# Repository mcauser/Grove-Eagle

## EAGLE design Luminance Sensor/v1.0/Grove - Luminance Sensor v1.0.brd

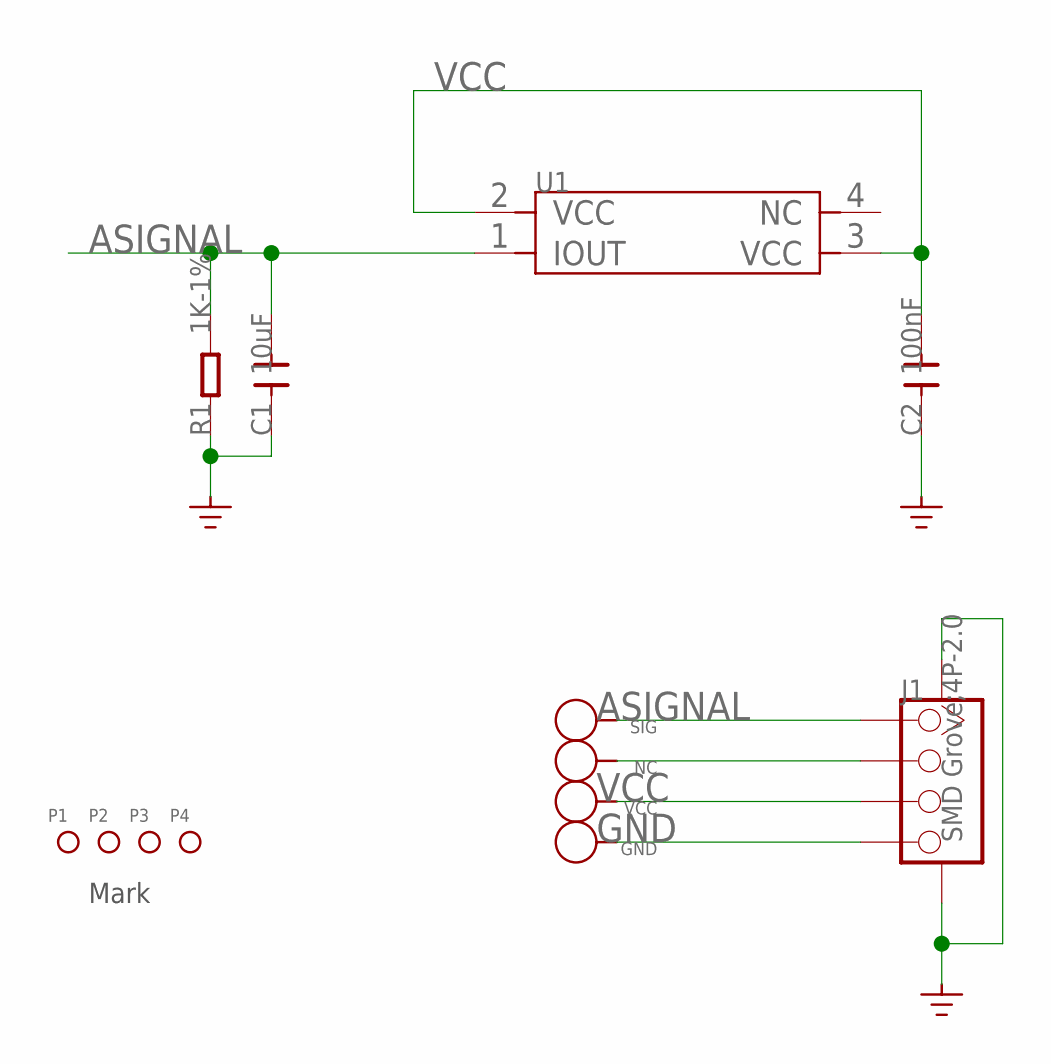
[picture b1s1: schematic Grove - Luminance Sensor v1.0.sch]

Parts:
C1: 10uF; C0603
C2: 100nF; C0603
GND: PAD-TEST-POINT'4545'; TP_4545
J1: SMD Grove;4P-2.0; 4P-SMD-2.0
NC: PAD-TEST-POINT'4545'; TP_4545
P1, P2, P3, P4: PAD-MARK; ROUND-MARK-1.0
R1: 1K-1%; R0603
SIG: PAD-TEST-POINT'4545'; TP_4545
U1: SENSOR-APDS-9002; 4P-SMD-2X1.25X0.8H
VCC: PAD-TEST-POINT'4545'; TP_4545

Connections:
ASIGNAL: C1.2, J1.1, R1.2, SIG.T, U1.1 (IOUT)
GND: C1.1, C2.1, GND.T, J1.4, J1.SS1, J1.SS2, R1.1
unnamed: J1.2, NC.T
VCC: C2.2, J1.3, U1.2 (VCC), U1.3 (VCC), VCC.T

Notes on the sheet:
Mark

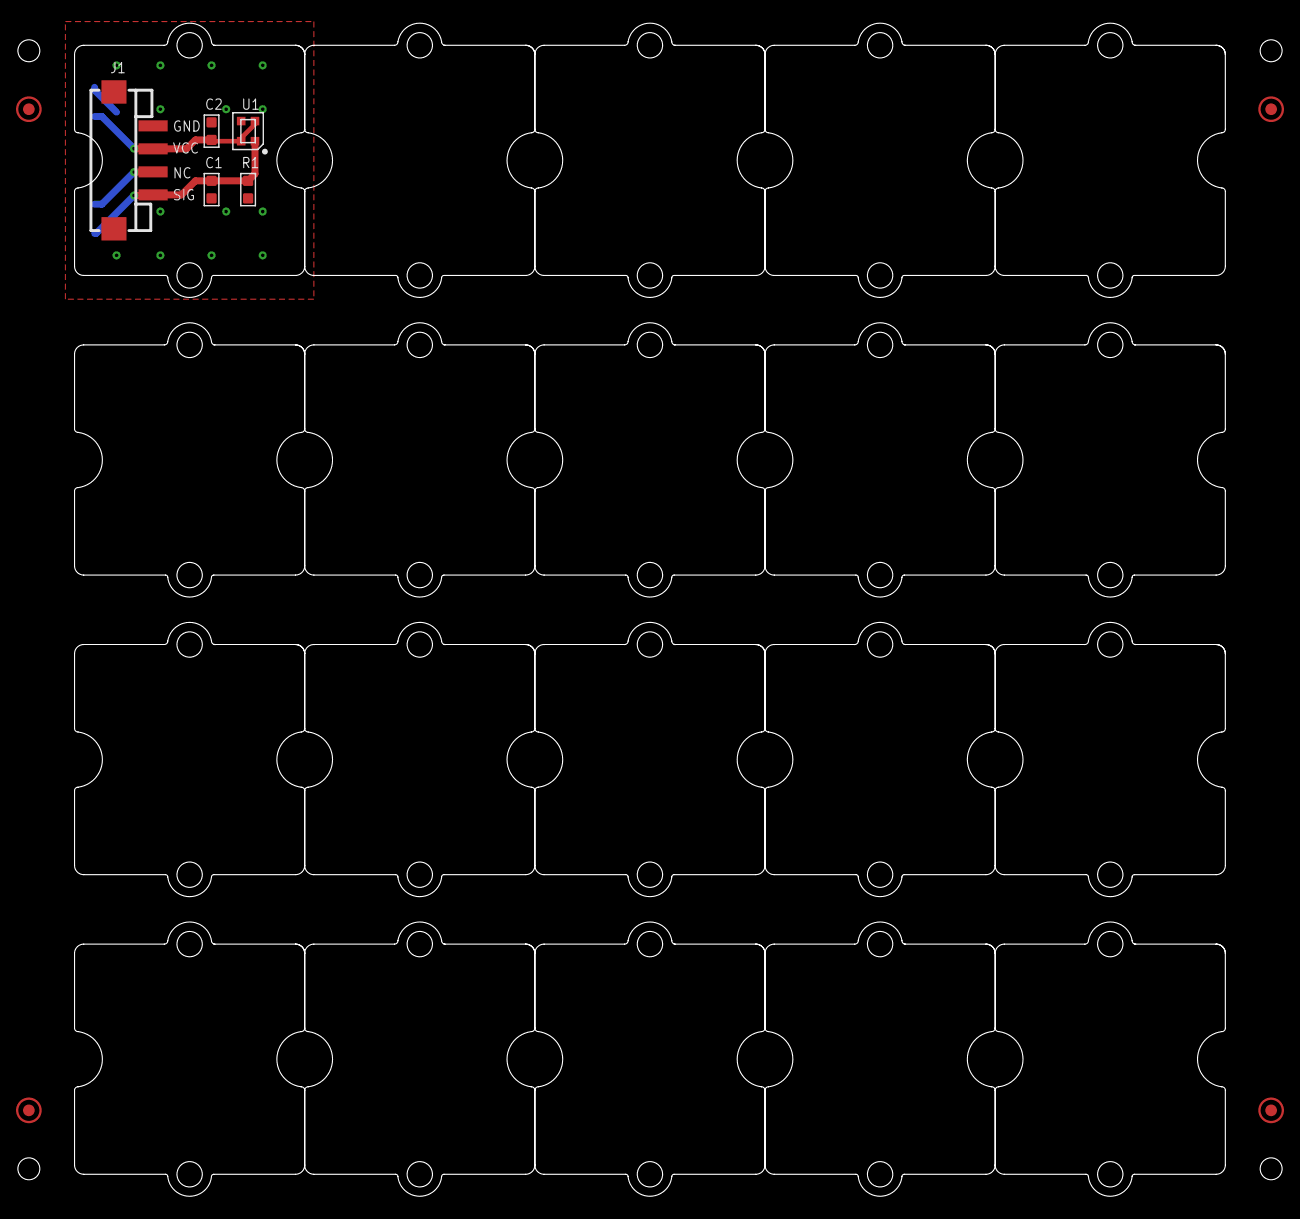
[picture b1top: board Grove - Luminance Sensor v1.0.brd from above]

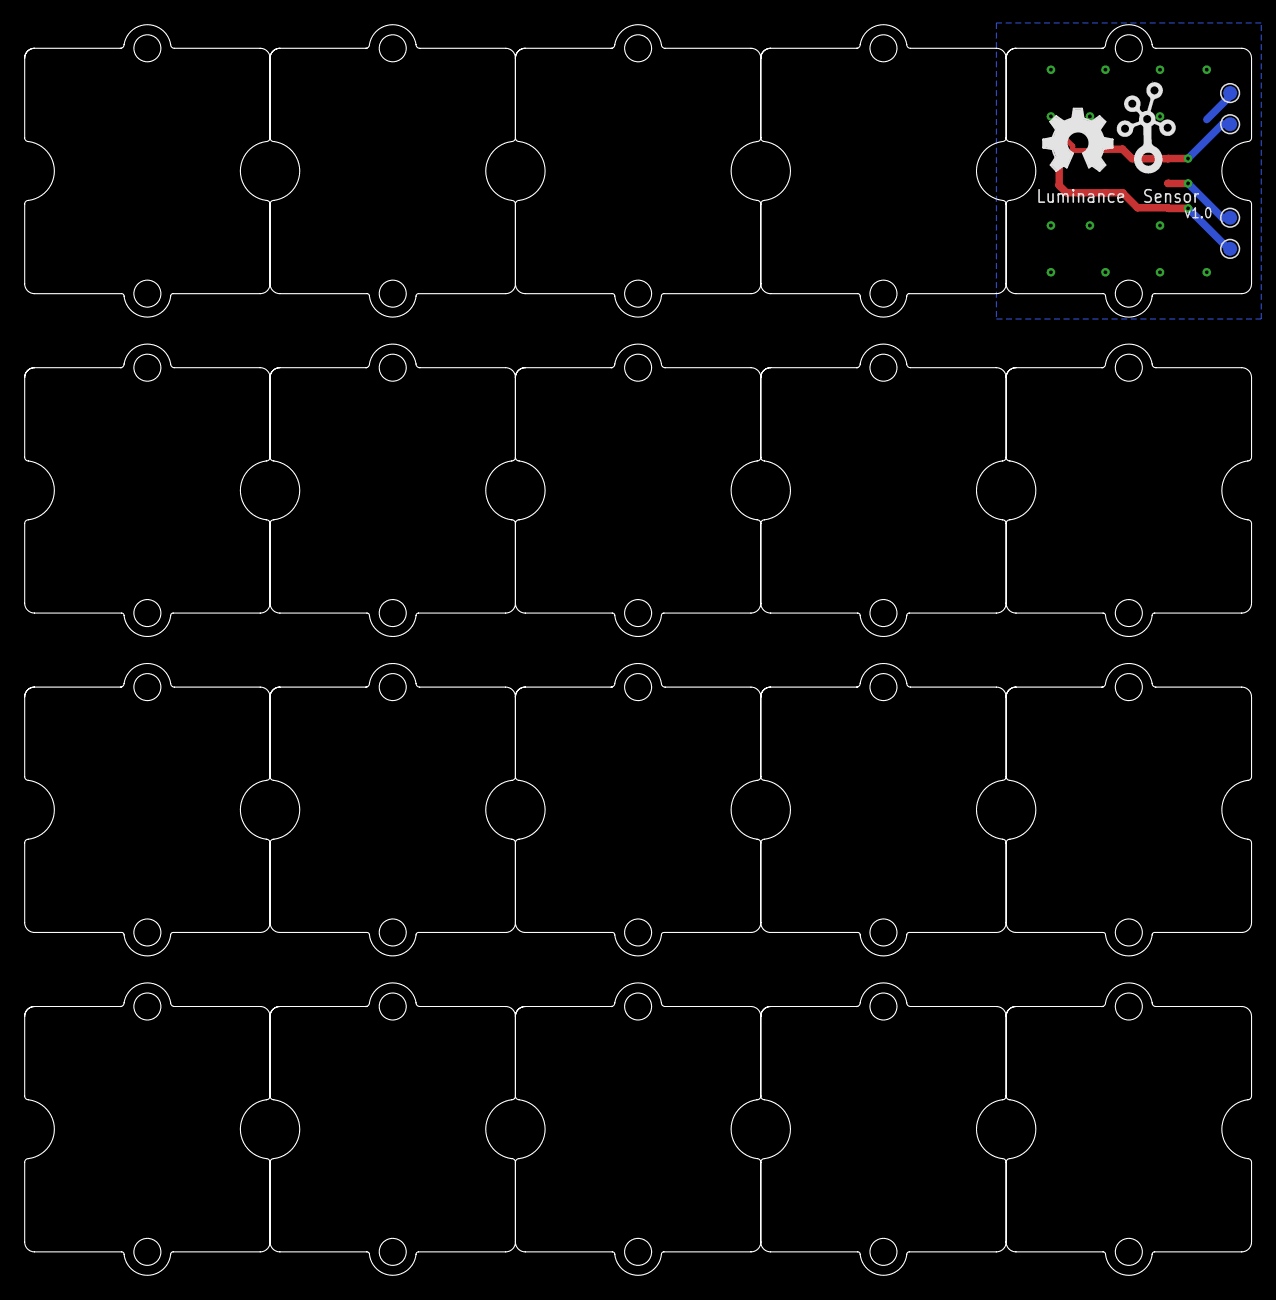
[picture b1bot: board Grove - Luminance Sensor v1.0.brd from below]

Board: 2 copper layers, 100.0 x 101.9 mm, 35 parts (6 on the bottom side), 4 nets.

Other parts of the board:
U$1, U$9, U$10, U$11, U$12, U$13, U$14, U$15, U$16, U$17, U$18, U$19, U$20, U$21, U$22, U$23, U$24, U$25, U$26, U$27: 1U-DIM-W/-DRILL
U$4: OSHW_FILLX200_NOTEXT
U$5: TWIGLOGO

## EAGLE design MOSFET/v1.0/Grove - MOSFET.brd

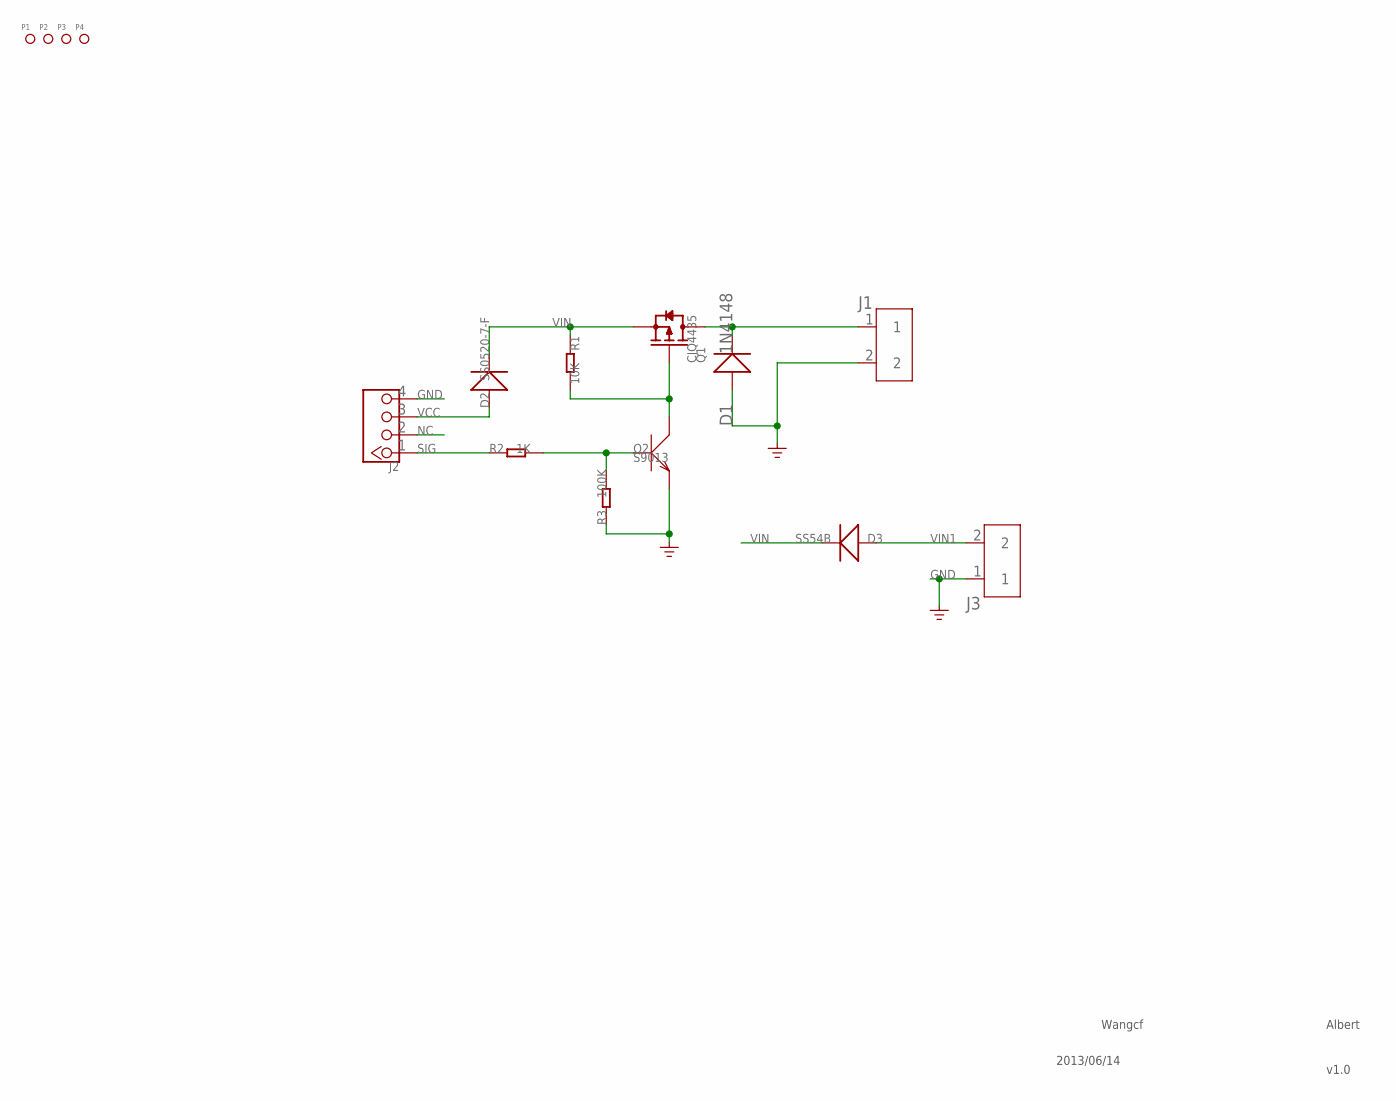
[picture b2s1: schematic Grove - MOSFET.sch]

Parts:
D1: 1N4148; DO-35-SMD
D2: SS0520-7-F; SOD123
D3: SS54B; SMB
J1, J3: SCREW-TERMINAL-2P'5.0-10.6X10X14.8H'; 2P-5.0-10.6X10X14.8H
J2: TWIG-4P-2.0-2.0; 4P-2.0
P1, P2, P3, P4: PAD-MARK; ROUND-MARK-1.0
Q1: CJQ4435; SOP8
Q2: S9013; SOT23
R1: 10K; R0603
R2: 1K; R0603
R3: 100K; R0603

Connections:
GND: D1.A (+), J1.2, J2.4, J3.1, Q2.2 (E), R3.1
unnamed: Q2.1 (B), R2.2, R3.2
unnamed: D1.C (-), J1.1, Q1.5 (D), Q1.6 (D), Q1.7 (D), Q1.8 (D)
unnamed: Q1.4 (G), Q2.3 (C), R1.2
NC: J2.2
SIG: J2.1, R2.1
VCC: D2.+, J2.3
VIN: D2.-, D3.-, Q1.1 (S), Q1.2 (S), Q1.3 (S), R1.1
VIN1: D3.+, J3.2

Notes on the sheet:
Wangcf
v1.0
2013/06/14
Albert

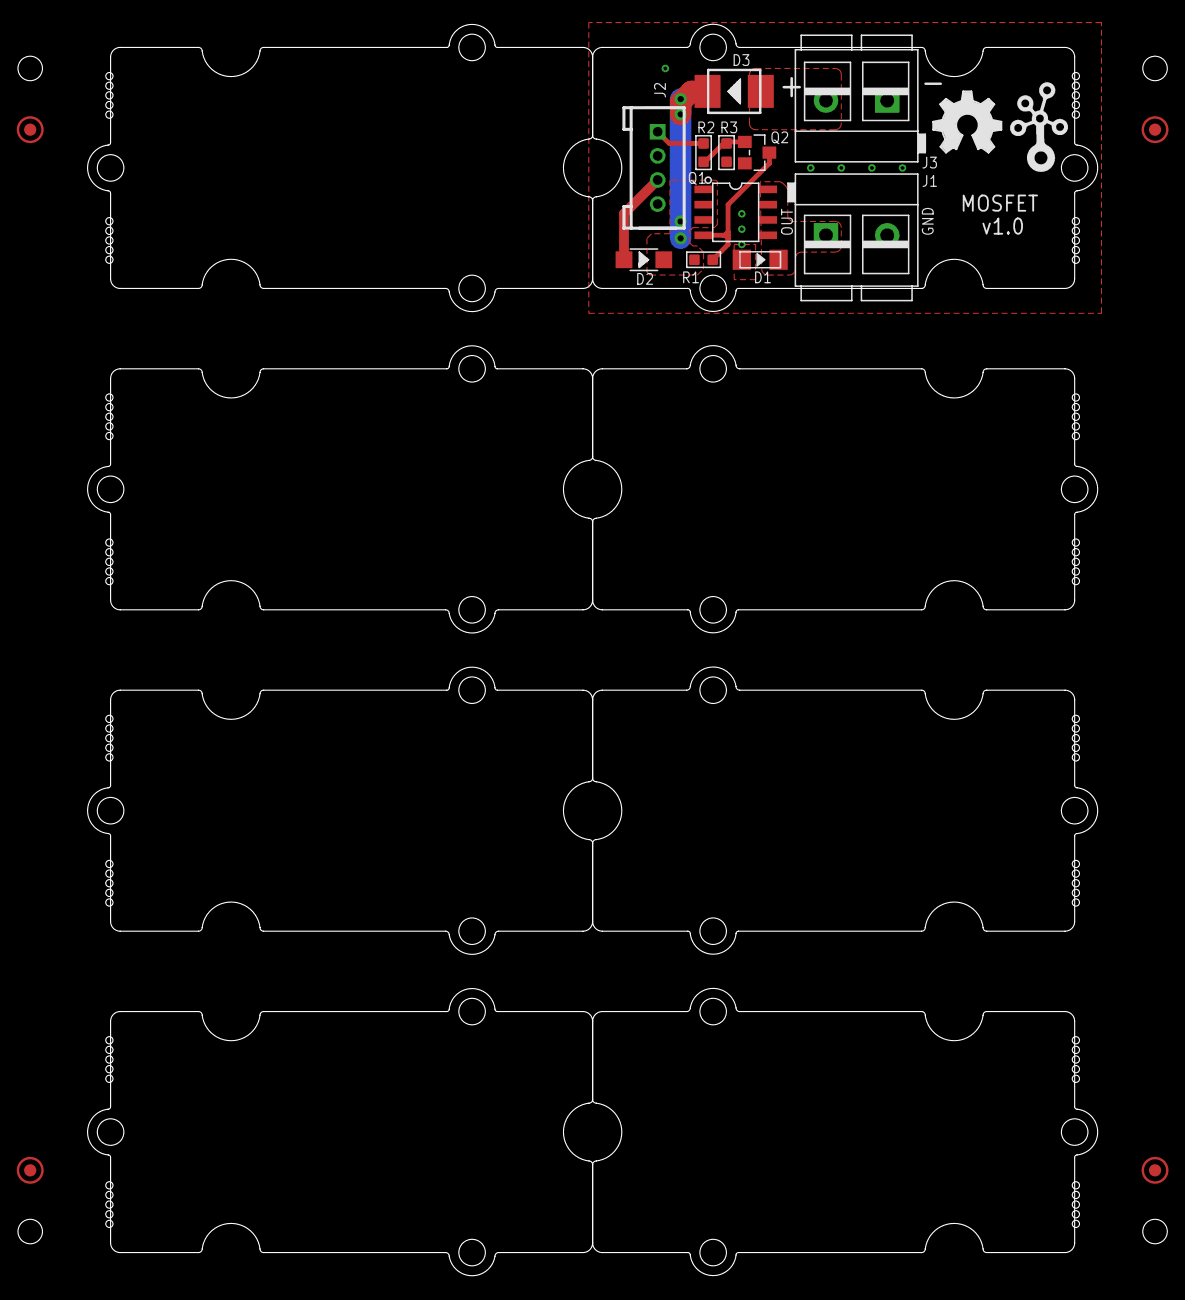
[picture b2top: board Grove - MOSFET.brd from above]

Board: 2 copper layers, 83.8 x 103.9 mm, 25 parts (0 on the bottom side), 8 nets.

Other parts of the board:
U$5, U$8, U$9, U$10, U$11, U$12, U$13, U$14: 2U-DIM-W/DRILL
U$6: TWIGLOGO
U$7: OSHW_FILLX200_NOTEXT

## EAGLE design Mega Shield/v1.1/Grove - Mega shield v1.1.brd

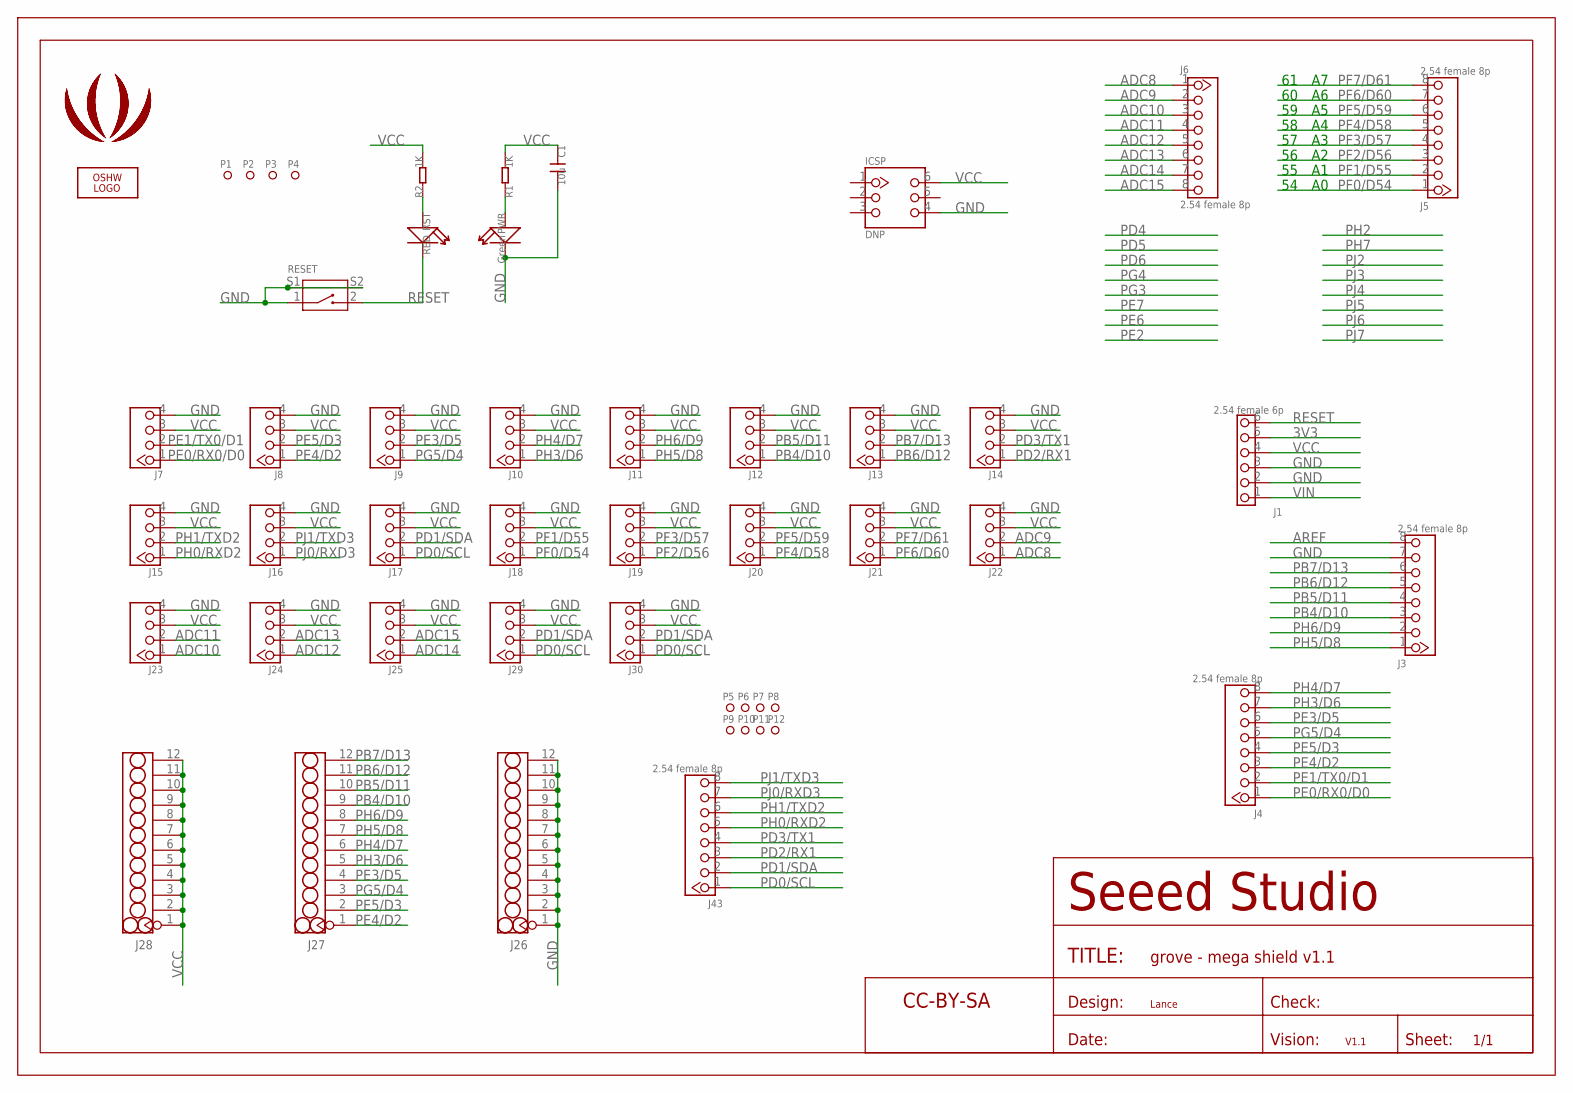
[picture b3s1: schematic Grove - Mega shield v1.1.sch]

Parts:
C1: 10u; 0805
ICSP: DNP; 2X3P-2.54-LEADED-60/35
J1: 2.54 female 6p; 6P-2.54-LEADED
J3, J4, J5, J6, J43: 2.54 female 8p; 8P-2.54-LEADED
J7, J14, J15, J16, J17: TWIG-2.0-LEADED'90D'; 4P-LEADED-2.0-90
J8, J9, J10, J11, J12, J13, J18, J19, J20, J21, J22, J23, J24, J25, J29, J30: TWIG-2.0-LEADED; 4P-LEADED-2.0
J26, J27, J28: HEADER-12P-2.54; 12P-2.54-LEADED
LOGO1: LOGO-OSHW-FILLX0200-NT; OSHW_FILLX200_NOTEXT
P1, P2, P3, P4, P5, P6, P7, P8, P9, P10, P11, P12: PAD-MARK'ANNULAR'; ROUND-MARK-1.0
PWR: Green; D0603
R1, R2: 1K; 0402
RESET: BUTTON-2+2P'TS-1188E'; 4P-SMD-L7.0*W3.5*H3.5MM-90D
RST: RED; D0603
U$1: LOGO-SEEEDSTUDIO-SILK; LOGO_SILK
U$2: LOGO-SEEEDSTUDIO-COPPER; LOGO_COPPER
U$3: SEEEDSTUDIO-OPEN-SCH-FRAME; SEEEDSTUDIO-PCB-FRAME

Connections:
3V3: J1.5
ADC8: J6.1, J22.1
ADC9: J6.2, J22.2
ADC10: J6.3, J23.1
ADC11: J6.4, J23.2
ADC12: J6.5, J24.1
ADC13: J6.6, J24.2
ADC14: J6.7, J25.1
ADC15: J6.8, J25.2
AREF: J3.8
GND: C1.2, ICSP.4, J1.2, J1.3, J3.7, J7.4, J8.4, J9.4, J10.4, J11.4, J12.4, J13.4, J14.4, J15.4, J16.4, J17.4, J18.4, J19.4, J20.4, J21.4, J22.4, J23.4, J24.4, J25.4, J26.1, J26.2, J26.3, J26.4, J26.5, J26.6, J26.7, J26.8, J26.9, J26.10, J26.11, J26.12, J29.4, J30.4, PWR.-, RESET.1, RESET.S1, RESET.S2
unnamed: PWR.+, R1.1
unnamed: R2.1, RST.+
PB4/D10: J3.3, J12.1, J27.9
PB5/D11: J3.4, J12.2, J27.10
PB6/D12: J3.5, J13.1, J27.11
PB7/D13: J3.6, J13.2, J27.12
PD0/SCL: J17.1, J29.1, J30.1, J43.1
PD1/SDA: J17.2, J29.2, J30.2, J43.2
PD2/RX1: J14.1, J43.3
PD3/TX1: J14.2, J43.4
PE0/RX0/D0: J4.1, J7.1
PE1/TX0/D1: J4.2, J7.2
PE3/D5: J4.6, J9.2, J27.4
PE4/D2: J4.3, J8.1, J27.1
PE5/D3: J4.4, J8.2, J27.2
PF0/D54: J5.1, J18.1
PF1/D55: J5.2, J18.2
PF2/D56: J5.3, J19.1
PF3/D57: J5.4, J19.2
PF4/D58: J5.5, J20.1
PF5/D59: J5.6, J20.2
PF6/D60: J5.7, J21.1
PF7/D61: J5.8, J21.2
PG5/D4: J4.5, J9.1, J27.3
PH0/RXD2: J15.1, J43.5
PH1/TXD2: J15.2, J43.6
PH3/D6: J4.7, J10.1, J27.5
PH4/D7: J4.8, J10.2, J27.6
PH5/D8: J3.1, J11.1, J27.7
PH6/D9: J3.2, J11.2, J27.8
PJ0/RXD3: J16.1, J43.7
PJ1/TXD3: J16.2, J43.8
RESET: J1.6, RESET.2, RST.-
VCC: C1.1, ICSP.6, J1.4, J7.3, J8.3, J9.3, J10.3, J11.3, J12.3, J13.3, J14.3, J15.3, J16.3, J17.3, J18.3, J19.3, J20.3, J21.3, J22.3, J23.3, J24.3, J25.3, J28.1, J28.2, J28.3, J28.4, J28.5, J28.6, J28.7, J28.8, J28.9, J28.10, J28.11, J28.12, J29.3, J30.3, R1.2, R2.2
VIN: J1.1

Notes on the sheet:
Lance
V1.1

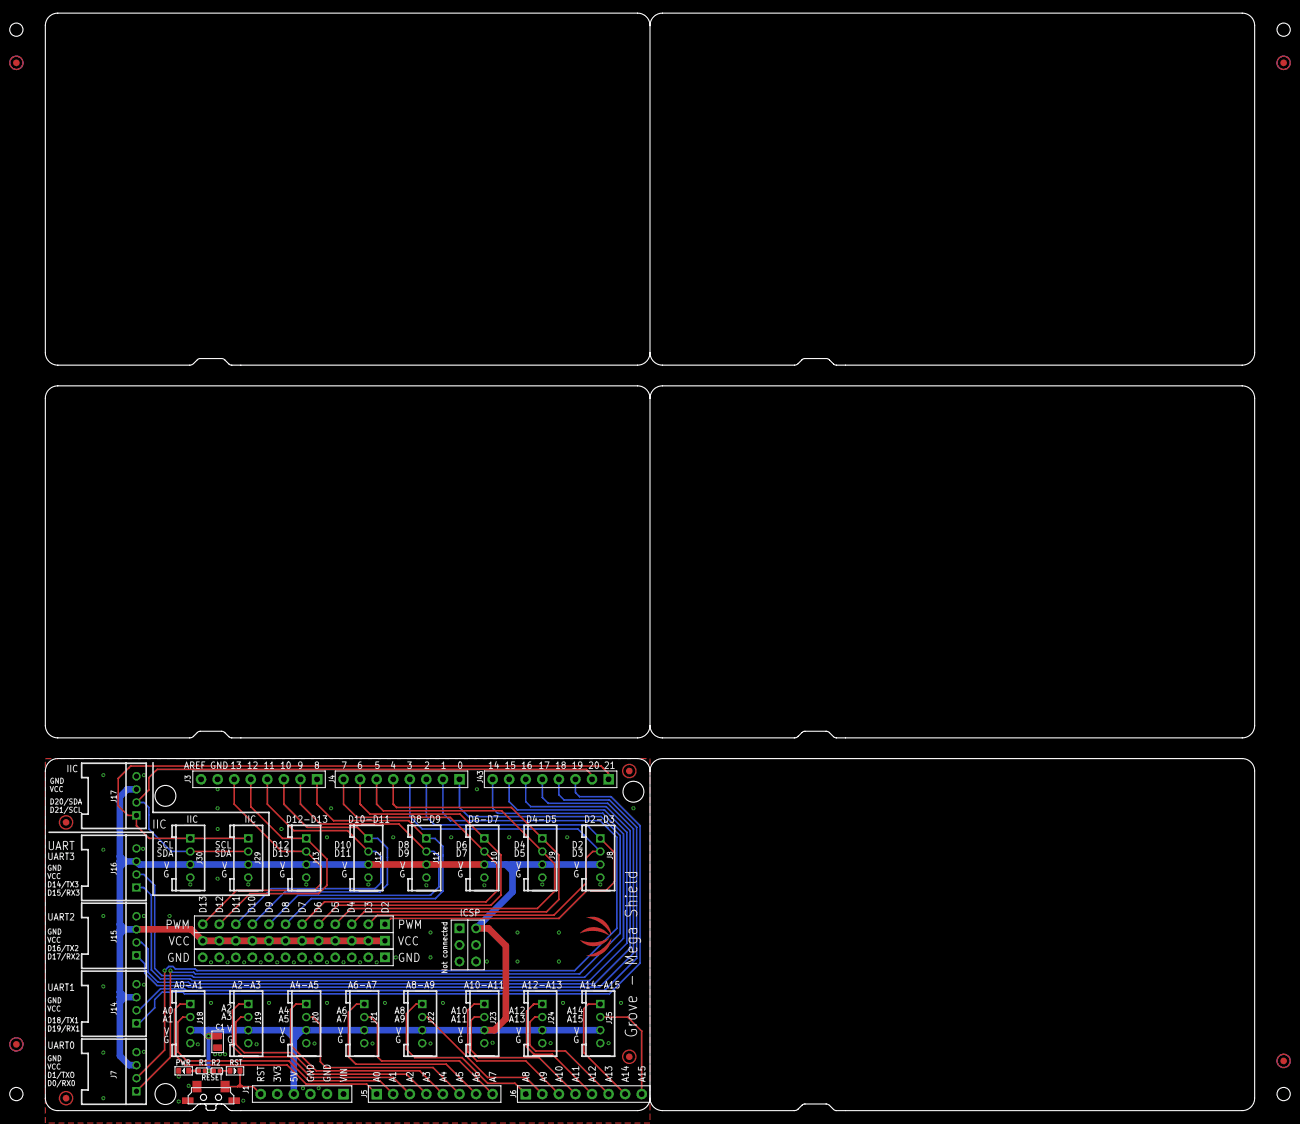
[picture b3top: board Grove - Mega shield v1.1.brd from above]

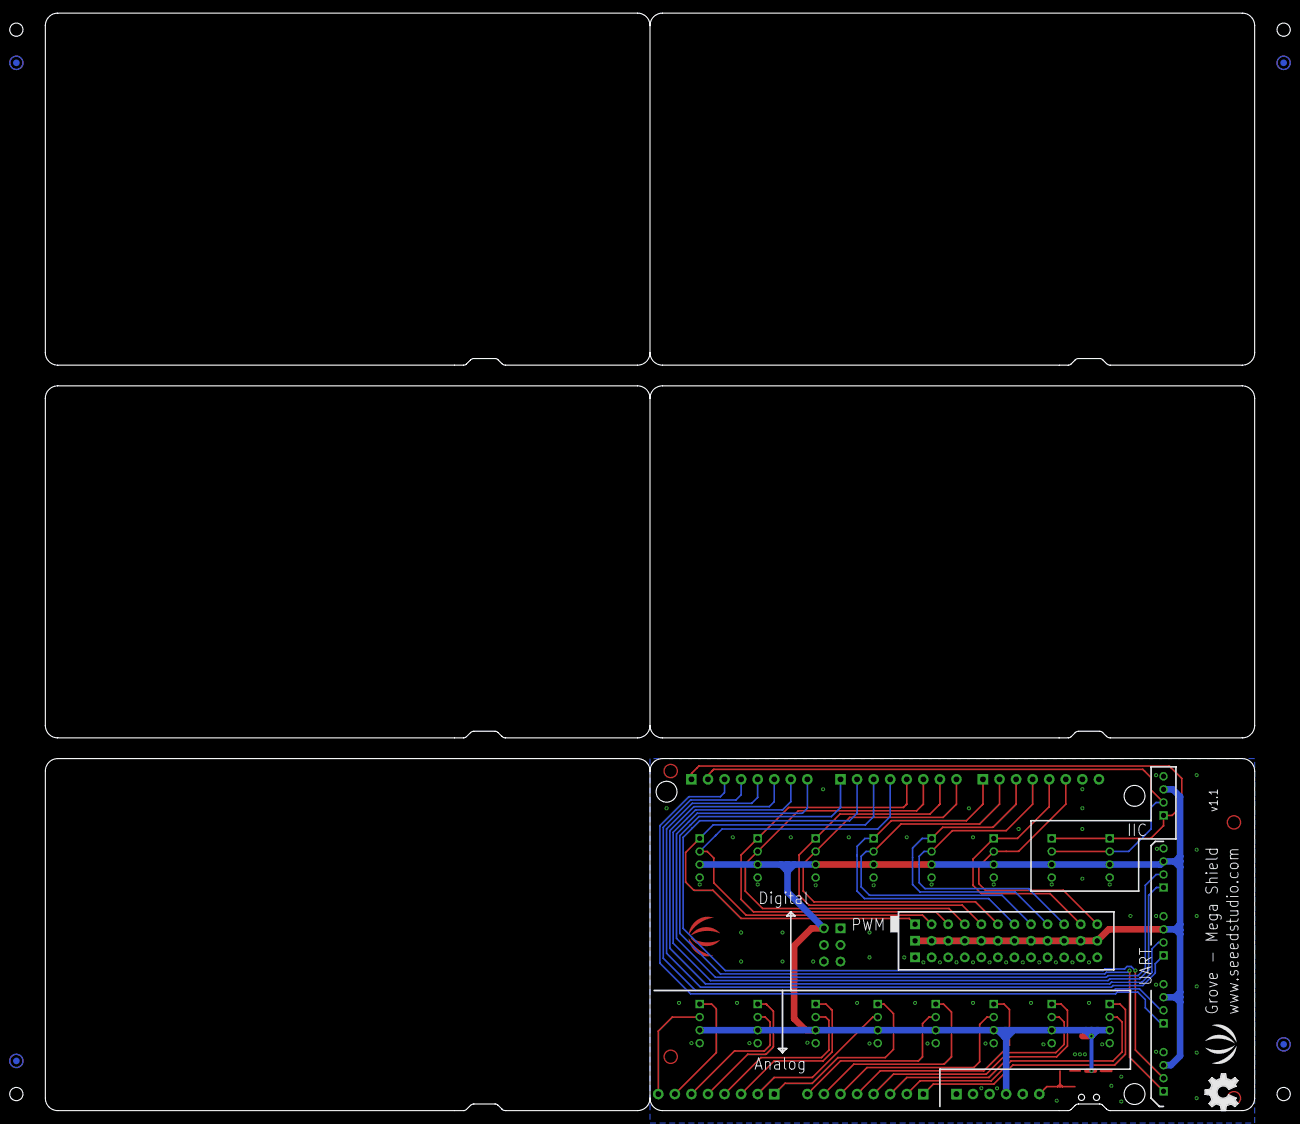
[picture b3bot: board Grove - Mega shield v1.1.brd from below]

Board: 2 copper layers, 185.4 x 54.0 mm, 53 parts (6 on the bottom side), 43 nets.

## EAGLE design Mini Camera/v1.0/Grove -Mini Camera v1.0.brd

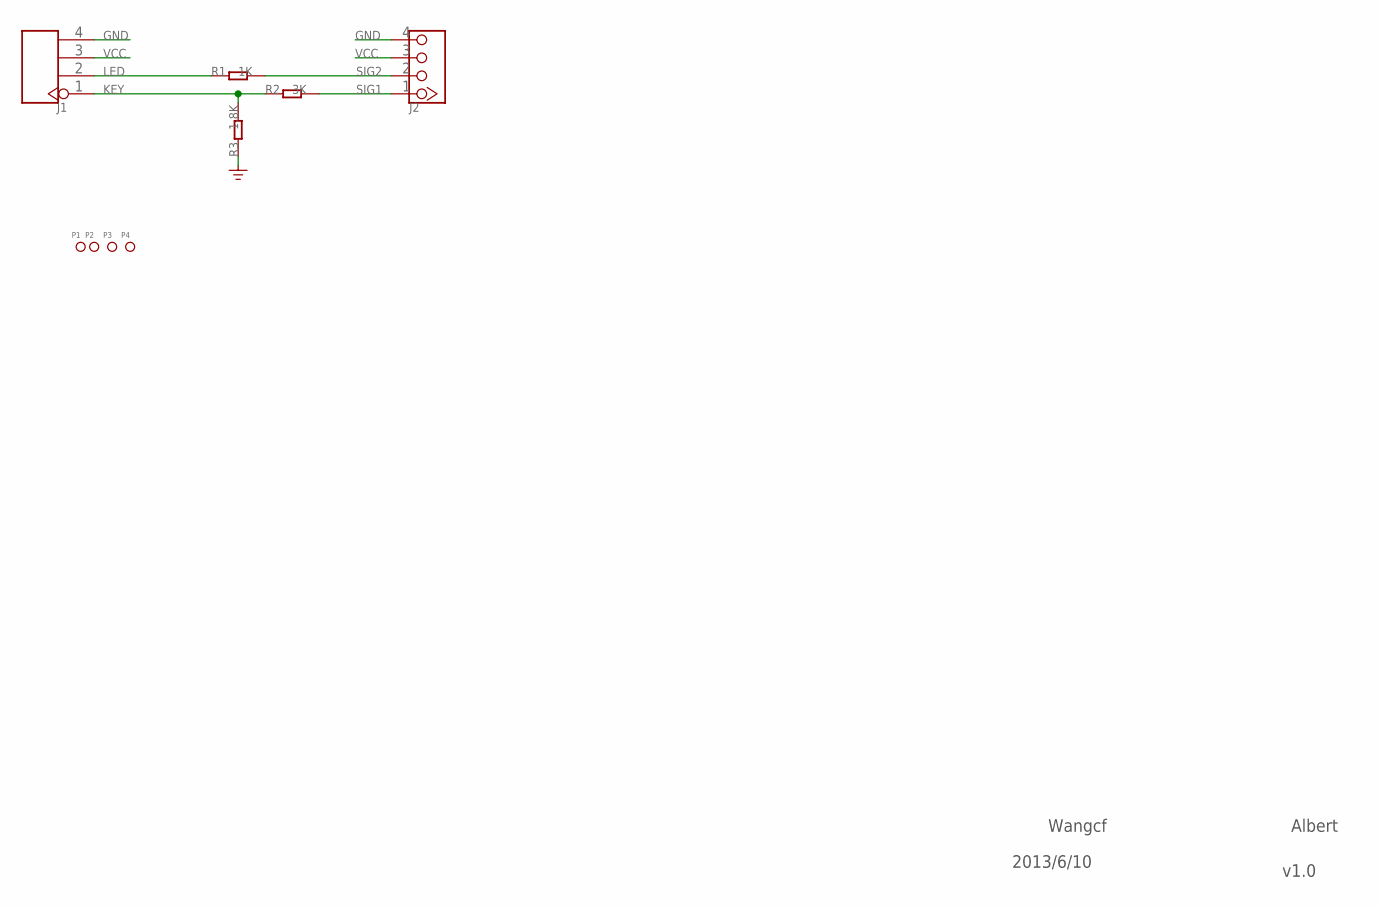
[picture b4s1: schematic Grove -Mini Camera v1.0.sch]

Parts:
J1: HEADER-4P-65/35MIL; 4P-65/35MIL
J2: TWIG-4P-2.0'90D'; 4P-2.0-90D
P1, P2, P3, P4: PAD-MARK; ROUND-MARK-1.0
R1: 1K; R0603
R2: 3K; R0603
R3: 1.8K; R0603

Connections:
GND: J1.4, J2.4, R3.1
KEY: J1.1, R2.1, R3.2
LED: J1.2, R1.1
SIG1: J2.1, R2.2
SIG2: J2.2, R1.2
VCC: J1.3, J2.3

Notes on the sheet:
Wangcf
Albert
2013/6/10
v1.0

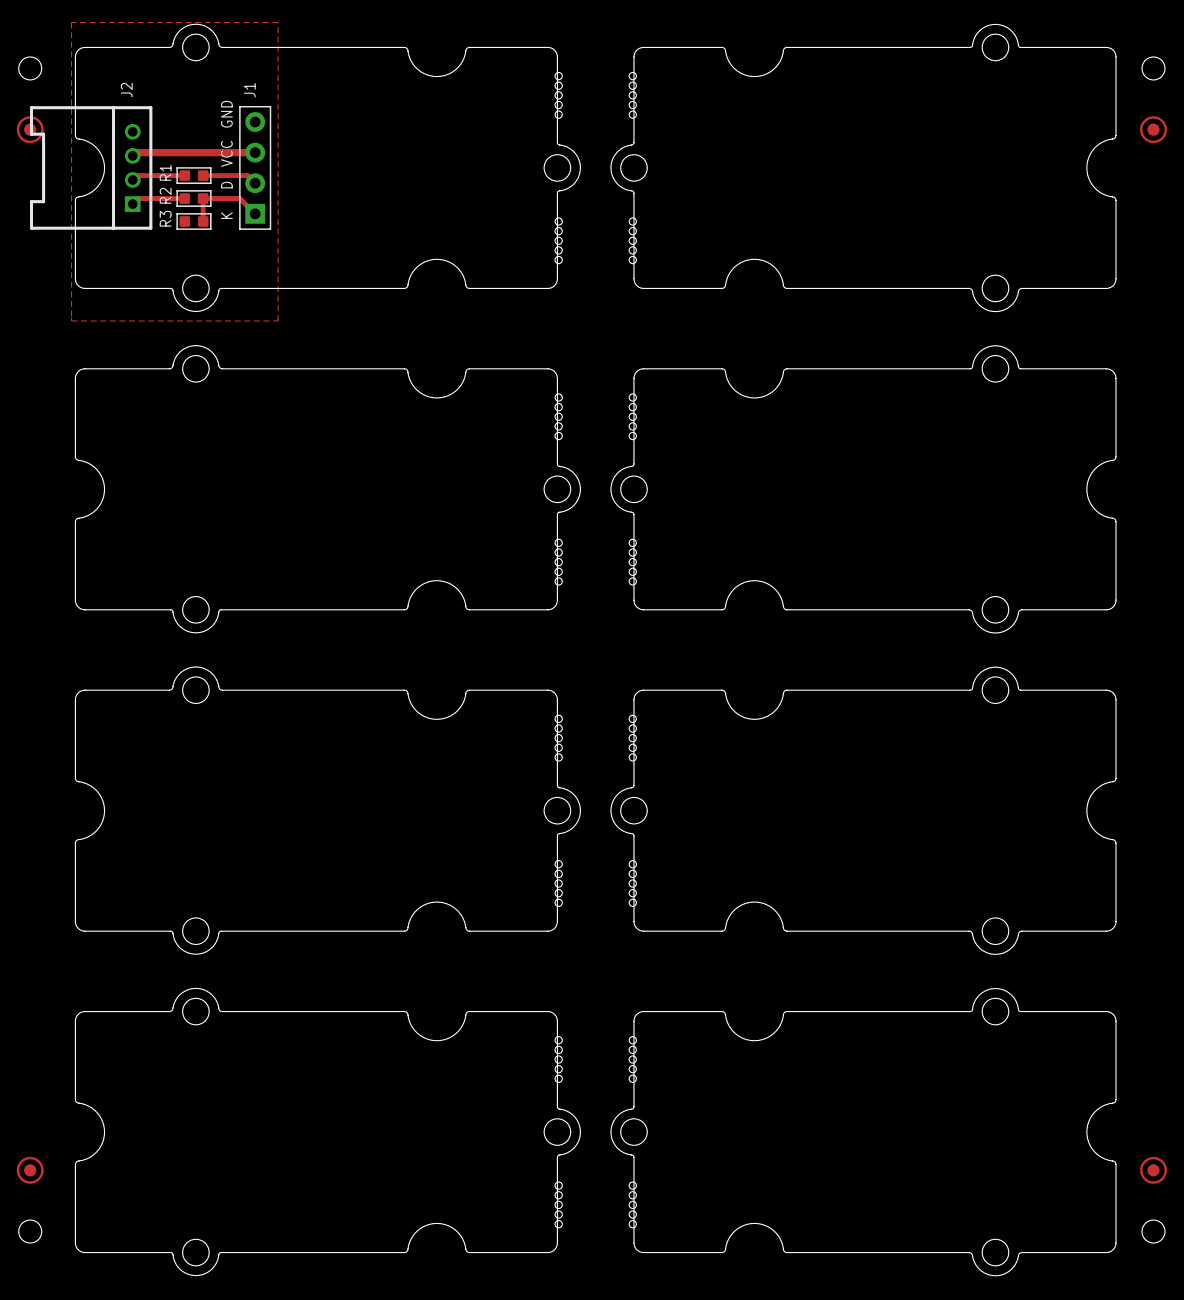
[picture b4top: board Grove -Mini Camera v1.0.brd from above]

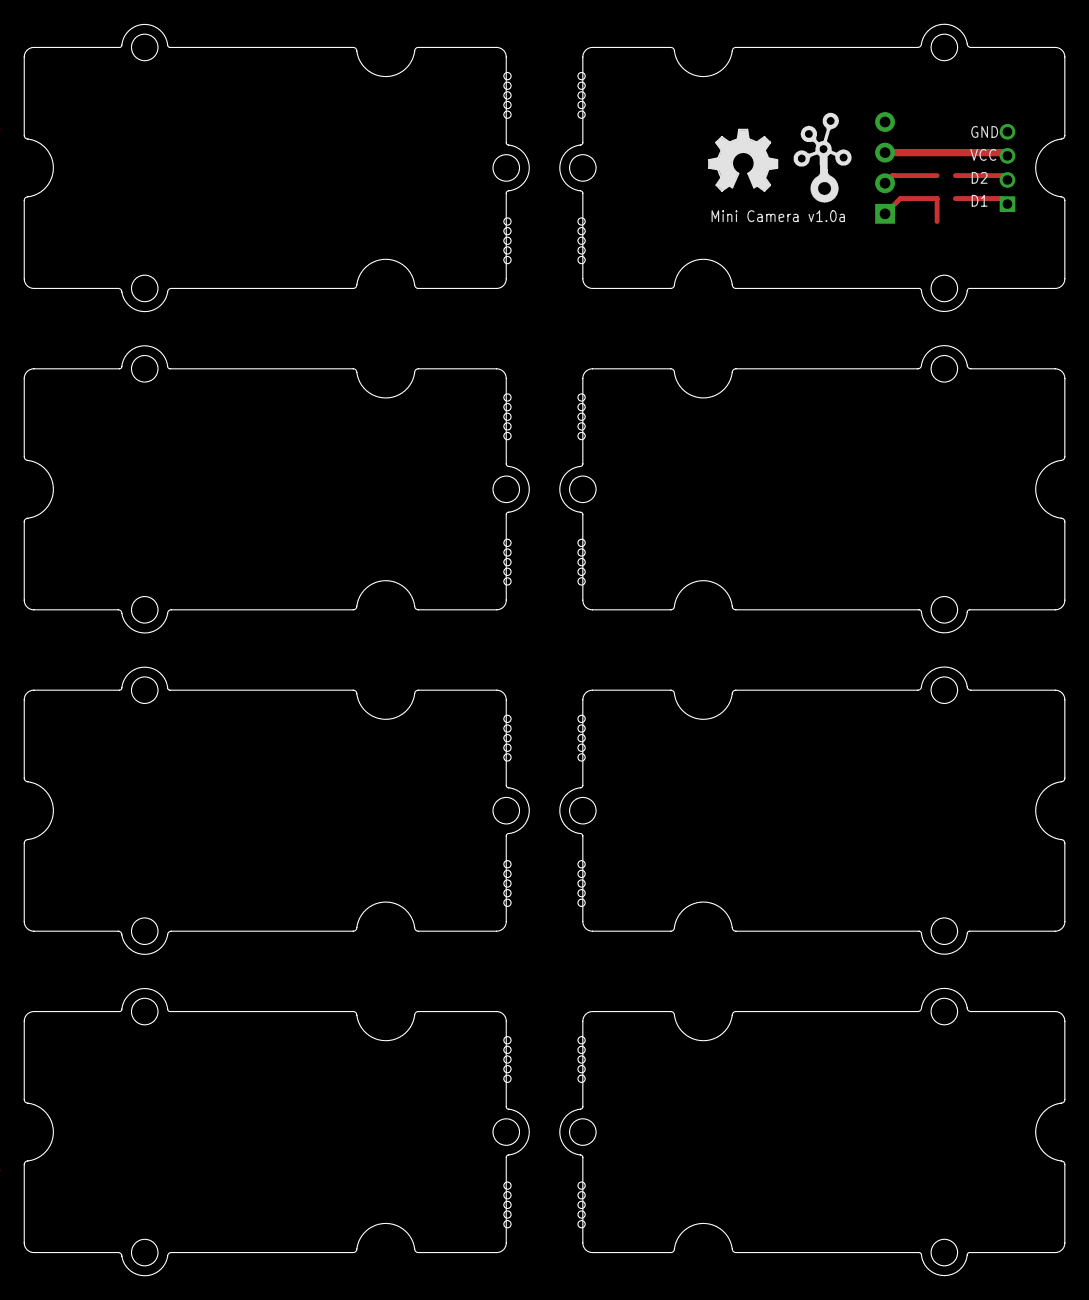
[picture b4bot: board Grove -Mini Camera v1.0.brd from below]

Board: 2 copper layers, 86.4 x 103.9 mm, 19 parts (2 on the bottom side), 6 nets.

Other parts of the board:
U$2: OSHW_FILLX200_NOTEXT
U$3: TWIGLOGO
U$5, U$6, U$7, U$8, U$9, U$10, U$11, U$12: 2U-DIM-W/DRILL

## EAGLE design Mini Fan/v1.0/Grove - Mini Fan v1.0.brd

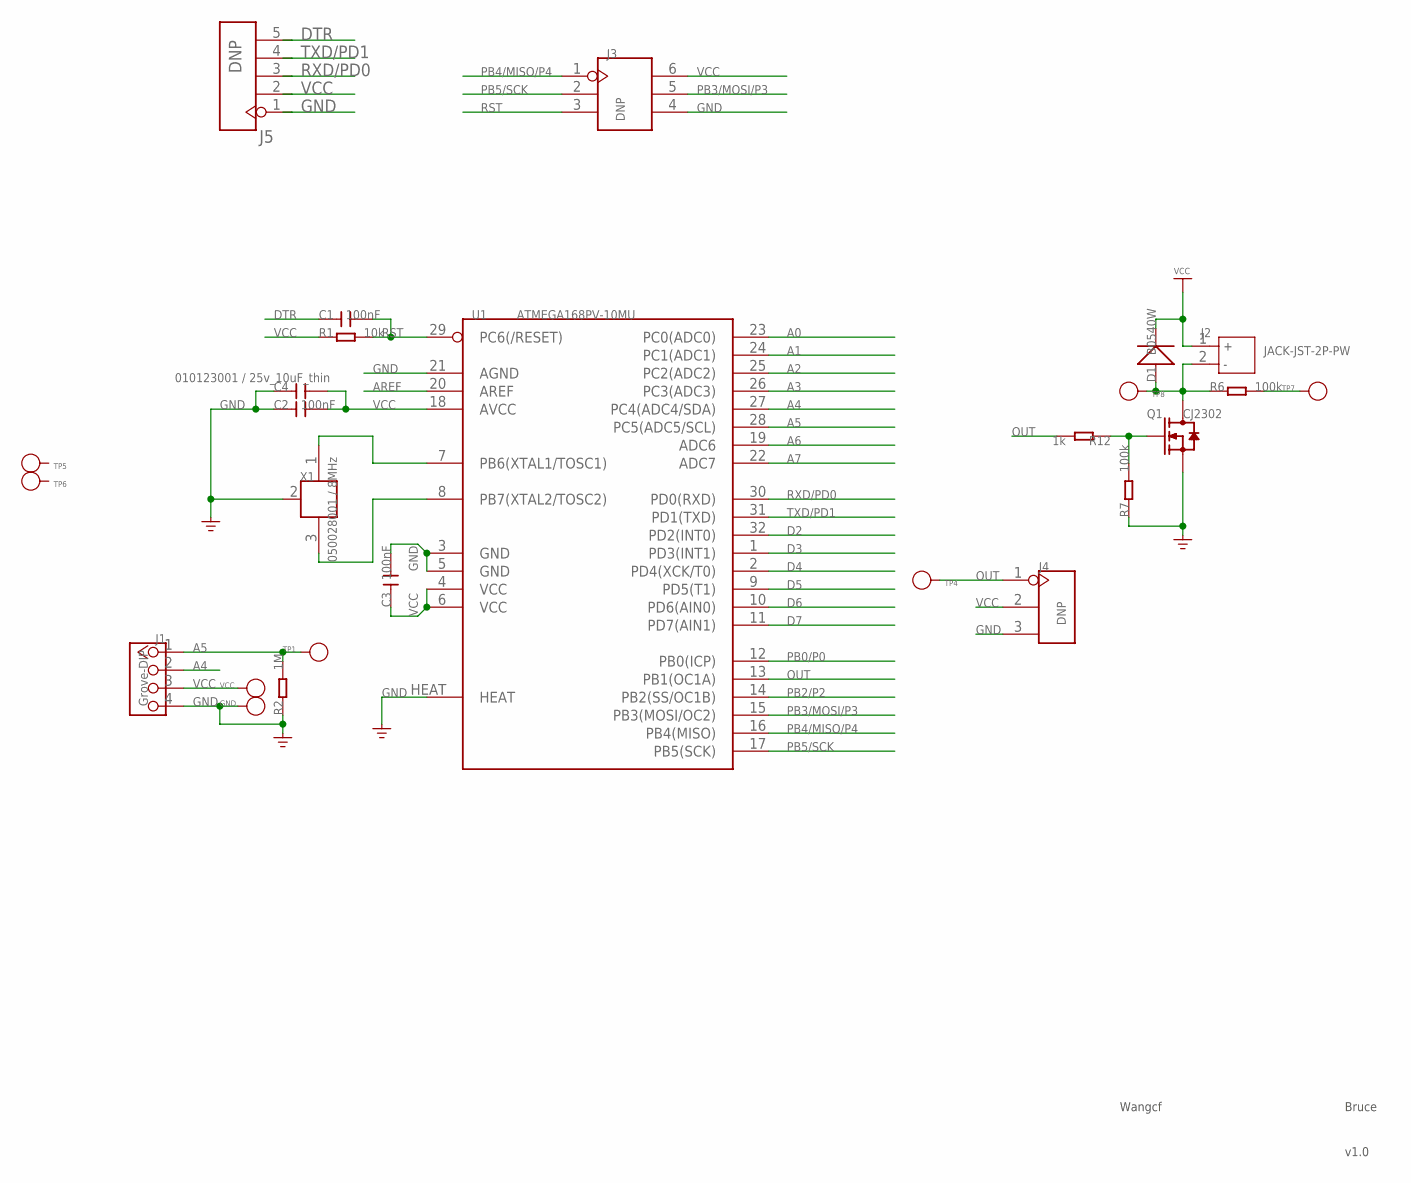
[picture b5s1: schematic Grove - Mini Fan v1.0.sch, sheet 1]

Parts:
C1, C2, C3: 100nF; C0603
C4: 010123001 / 25v_10uF_thin; C0805
D1: B0540W; SOD123
GND: PAD-TEST-POINT'4545'; TP_4545
J1: Grove-DIP; 4P-2.0
J2: JACK-JST-2P-PW; JST-2.0
J3: DNP; 2X3P-2.0
J4: DNP; 3P-2.54
J5: DNP; 5P-2.54
Q1: CJ2302; SOT23
R1: 10k; R0603
R2: 1M; R0603
R6, R7: 100k; R0603
R12: 1k; R0603
TP1, TP4, TP5, TP6, TP7, TP8: PAD-TEST-POINT'4545'; TP_4545
U1: ATMEGA168PV-10MU; MLF32X
VCC: PAD-TEST-POINT'4545'; TP_4545
X1: 050028001 / 8MHz; XTAL_3X2

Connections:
A0: U1.23 (PC0(ADC0))
A1: U1.24 (PC1(ADC1))
A2: U1.25 (PC2(ADC2))
A3: U1.26 (PC3(ADC3))
A4: J1.2, U1.27 (PC4(ADC4/SDA))
A5: J1.1, R2.2, TP1.T, U1.28 (PC5(ADC5/SCL))
A6: U1.19 (ADC6)
A7: U1.22 (ADC7)
AREF: U1.20 (AREF)
D2: U1.32 (PD2(INT0))
D3: U1.1 (PD3(INT1))
D4: U1.2 (PD4(XCK/T0))
D5: U1.9 (PD5(T1))
D6: U1.10 (PD6(AIN0))
D7: U1.11 (PD7(AIN1))
DTR: C1.1, J5.5
GND: C2.1, C3.2, C4.1, GND.T, J1.4, J3.4, J4.3, J5.1, Q1.2 (S), R2.1, R7.1, U1.3 (GND), U1.5 (GND), U1.21 (AGND), U1.HEAT, X1.2 (GND)
unnamed: D1.+, J2.2, Q1.3 (D), R6.1, TP8.T
unnamed: R6.2, TP7.T
unnamed: Q1.1 (G), R7.2, R12.1
unnamed: U1.7 (PB6(XTAL1/TOSC1)), X1.1
unnamed: U1.8 (PB7(XTAL2/TOSC2)), X1.3 (2)
OUT: J4.1, R12.2, TP4.T, U1.13 (PB1(OC1A))
PB0/P0: U1.12 (PB0(ICP))
PB2/P2: U1.14 (PB2(SS/OC1B))
PB3/MOSI/P3: J3.5, U1.15 (PB3(MOSI/OC2))
PB4/MISO/P4: J3.1, U1.16 (PB4(MISO))
PB5/SCK: J3.2, U1.17 (PB5(SCK))
RST: C1.2, J3.3, R1.2, U1.29 (PC6(/RESET))
RXD/PD0: J5.3, U1.30 (PD0(RXD))
TXD/PD1: J5.4, U1.31 (PD1(TXD))
VCC: C2.2, C3.1, C4.2, D1.-, J1.3, J2.1, J3.6, J4.2, J5.2, R1.1, U1.4 (VCC), U1.6 (VCC), U1.18 (AVCC), VCC.T

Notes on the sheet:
Wangcf
Bruce
v1.0

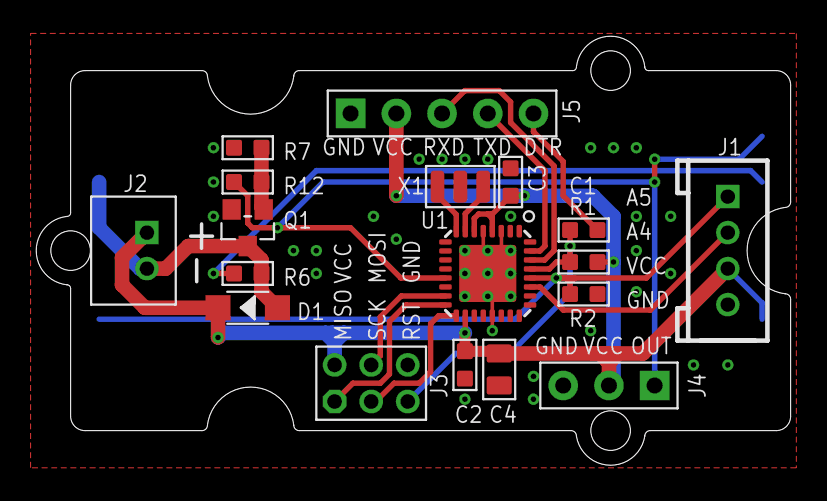
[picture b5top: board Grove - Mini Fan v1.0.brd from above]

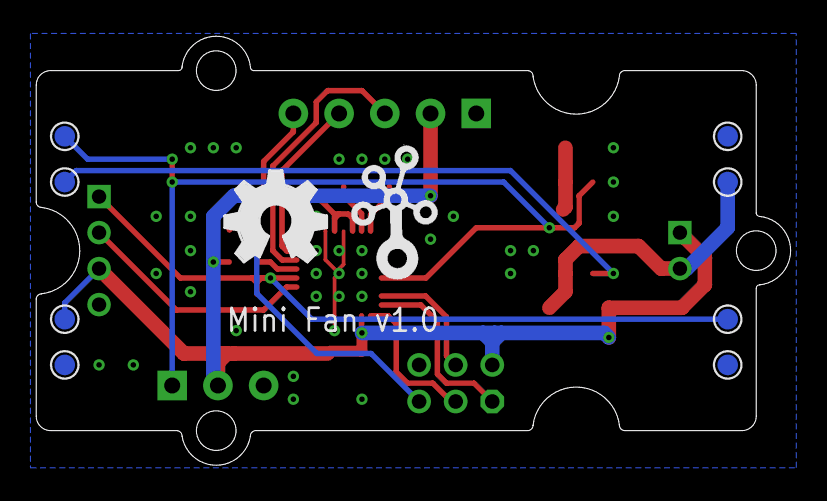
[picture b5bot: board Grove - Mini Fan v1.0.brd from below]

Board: 4 copper layers, 41.9 x 23.8 mm, 29 parts (10 on the bottom side), 17 nets.

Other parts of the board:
U$2: GROVE-2CONNECTOR
U$3: TWIGLOGO
U$6: OSHW_FILLX200_NOTEXT

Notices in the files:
parts and their libraries:
moudle-new: This work is licensed under the Creative Commons Attribution 4.0 International License.
To view a copy of this license,visit:
http://creativecommons.org/licenses/by-sa/4.0
moudle-new: CC-BY-SA
